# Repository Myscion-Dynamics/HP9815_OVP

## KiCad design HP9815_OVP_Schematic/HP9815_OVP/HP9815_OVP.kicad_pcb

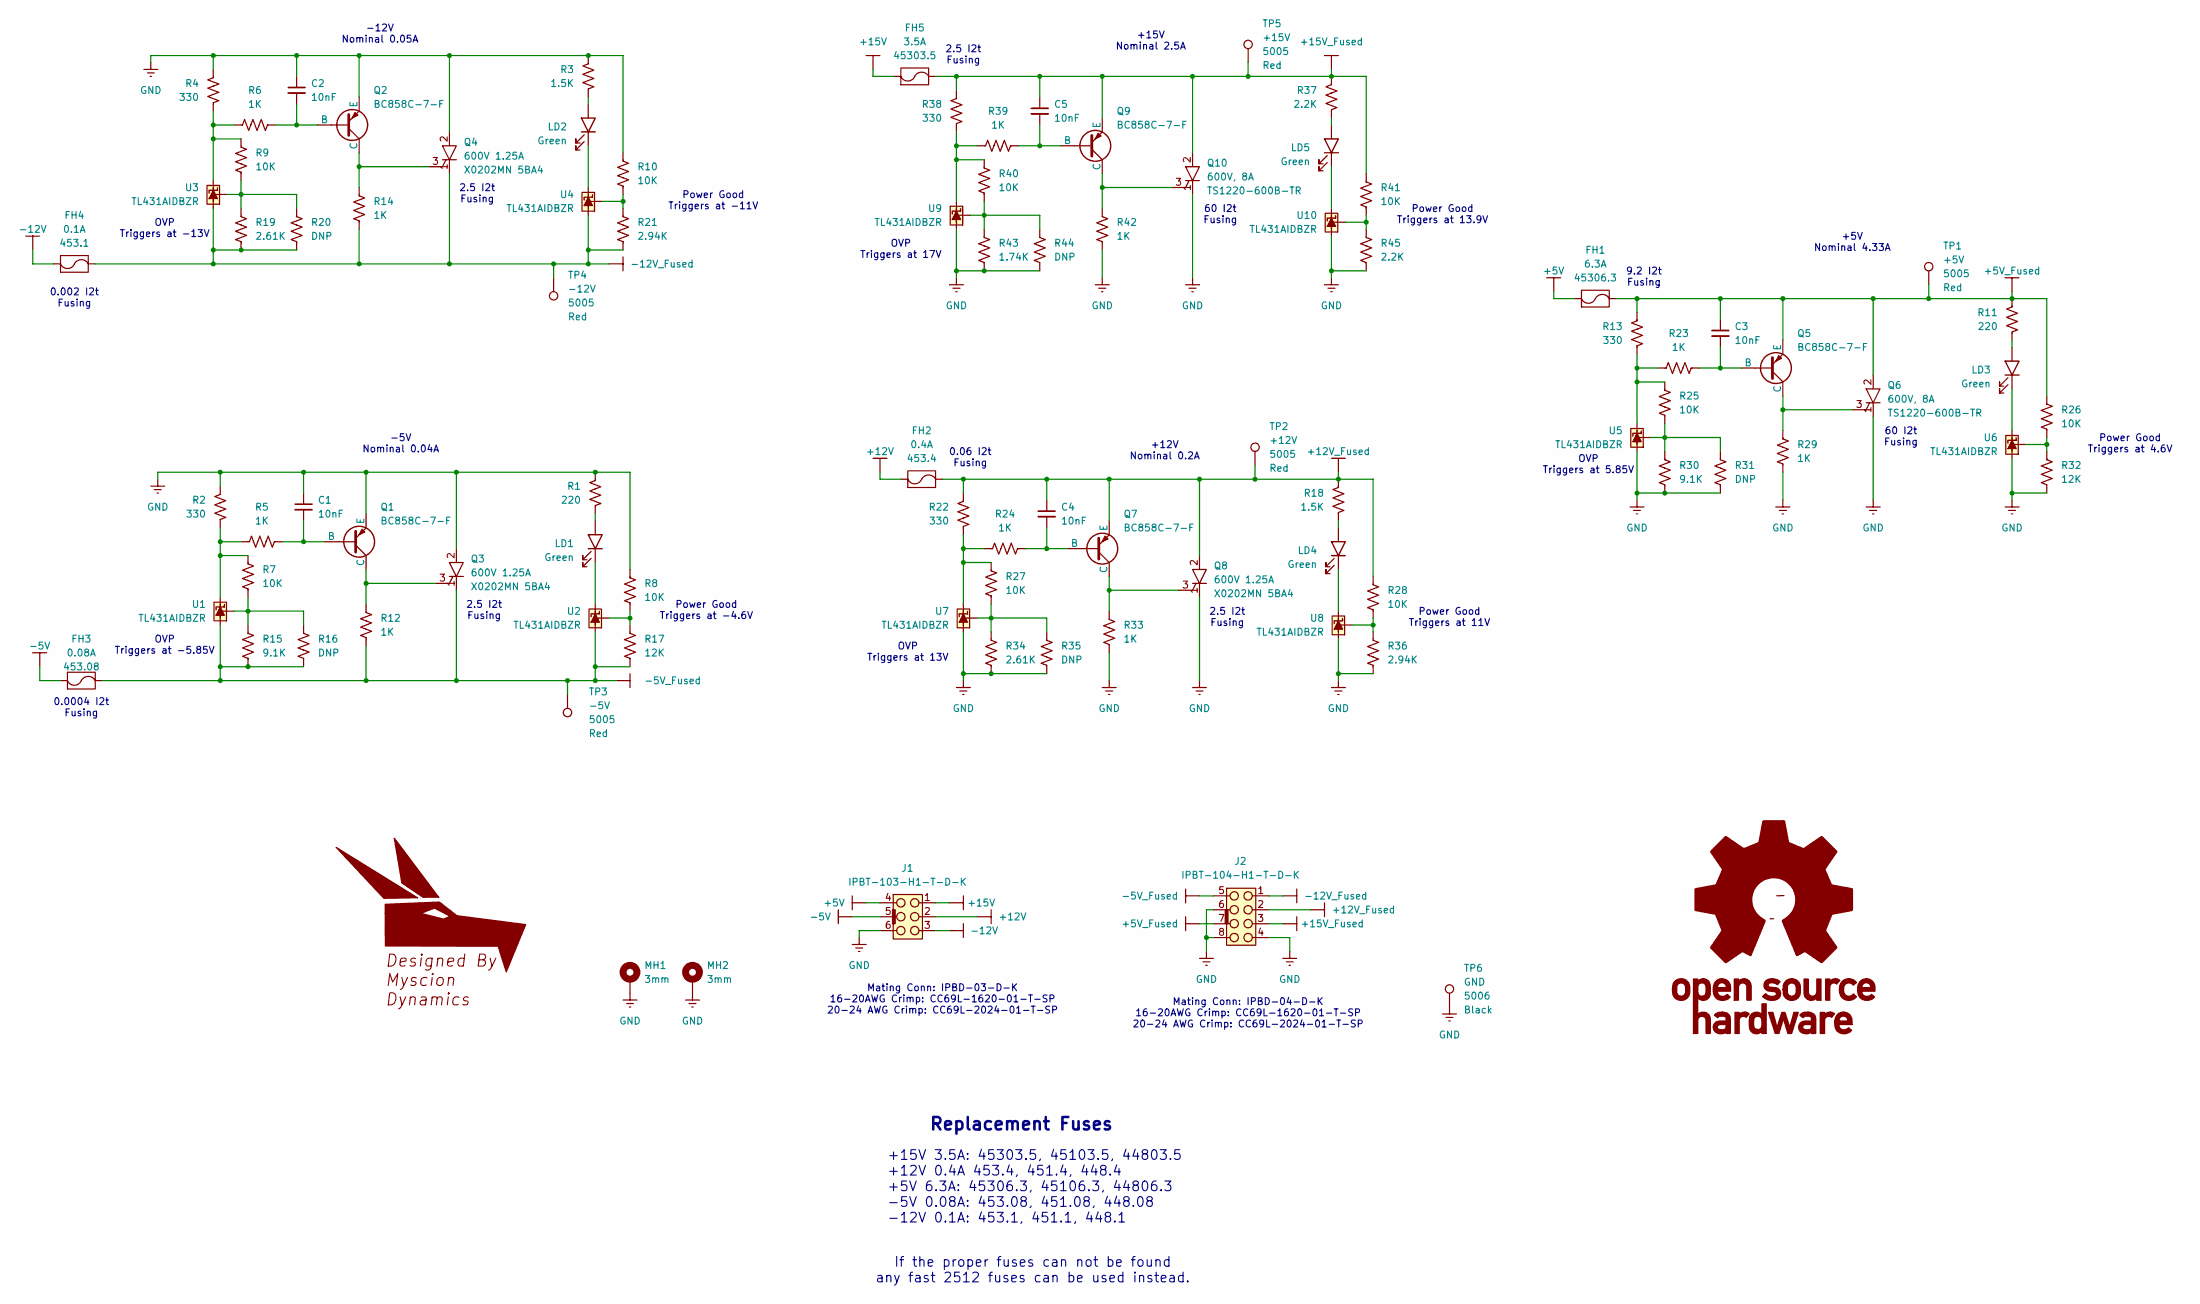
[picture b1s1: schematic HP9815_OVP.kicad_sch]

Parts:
C1, C2, C3, C4, C5: 10nF; C_0603_1608Metric_Pad1.08x0.95mm_HandSolder; Voltage 50V; Tolerance 10%; MPN 311-1085-6-ND
FH1: 6.3A; Fuseholder_Littelfuse_Nano2_154x; Voltage Rating 125V; MPN 15406.3
FH2: 0.4A; Fuseholder_Littelfuse_Nano2_154x; Voltage Rating 125V; MPN 154.4
FH3: 0.08A; Fuseholder_Littelfuse_Nano2_154x; Voltage Rating 125V; MPN 154.08
FH4: 0.1A; Fuseholder_Littelfuse_Nano2_154x; Voltage Rating 125V; MPN 154.1
FH5: 3.5A; Fuseholder_Littelfuse_Nano2_154x; Voltage Rating 125V; MPN 15403.5
GL1: Myscion_Dynamics_Main
GL2: OSHW-Logo_11.4x12mm_SilkScreen
J1: IPBT-103-H1-T-D-K; SAMTEC_IPBT-103-H1-T-D-K; Voltage 400VAC, 565VDC; MPN IPBT-103-H1-T-D-K
J2: IPBT-104-H1-T-D-K; SAMTEC_IPBT-104-H1-T-D-K; Voltage 400VAC, 565VDC; MPN IPBT-104-H1-T-D-K
LD1, LD2, LD3, LD4, LD5: Green; LED_0603_1608Metric_Green_Cath_Dot; MPN HSME-C191
MH1, MH2: 3mm; MountingHole_3.2mm_M3_Pad
Q1, Q2, Q5, Q7, Q9: BC858C-7-F; SOT-23-3_B-E-C; MPN BC858C-7-F
Q3, Q4, Q8: 600V 1.25A; SOT-223-3_TabPin2; MPN X0202MN 5BA4
Q6, Q10: 600V, 8A; TO-252-2; MPN TS1220-600B-TR
R1, R11: 220; R_0603_1608Metric_Pad0.98x0.95mm_HandSolder; MPN RC0603FR-07220RL
R2, R4, R13, R22, R38: 330; R_0603_1608Metric_Pad0.98x0.95mm_HandSolder; MPN RC0603FR-07330RL
R3, R18: 1.5K; R_0603_1608Metric_Pad0.98x0.95mm_HandSolder; MPN RC0603FR-071K5L
R5, R6, R12, R14, R23, R24, R29, R33, R39, R42: 1K; R_0603_1608Metric_Pad0.98x0.95mm_HandSolder; MPN RC0603FR-071KL
R7, R8, R9, R10, R25, R26, R27, R28, R40, R41: 10K; R_0603_1608Metric_Pad0.98x0.95mm_HandSolder; MPN RC0603FR-0710KL
R15, R30: 9.1K; R_0603_1608Metric_Pad0.98x0.95mm_HandSolder; MPN RC0603FR-079K1L
R16, R20, R31, R35, R44: DNP; R_0603_1608Metric_Pad0.98x0.95mm_HandSolder_DNP; MPN NA
R17, R32: 12K; R_0603_1608Metric_Pad0.98x0.95mm_HandSolder; MPN RC0603FR-0712KL
R19, R34: 2.61K; R_0603_1608Metric_Pad0.98x0.95mm_HandSolder; MPN RC0603FR-072K61L
R21, R36: 2.94K; R_0603_1608Metric_Pad0.98x0.95mm_HandSolder; MPN RC0603FR-072K94L
R37, R45: 2.2K; R_0603_1608Metric_Pad0.98x0.95mm_HandSolder; MPN RC0603FR-072K2L
R43: 1.74K; R_0603_1608Metric_Pad0.98x0.95mm_HandSolder; MPN RC0603FR-071K74L
TP1, TP2, TP3, TP4, TP5: TestPoint; TestPoint_Keystone_5005_Compact_Red; MPN 5005
TP6: TestPoint; TestPoint_Keystone_5006_Compact_Black; MPN 5006
U1, U2, U3, U4, U5, U6, U7, U8, U9, U10: TL431DBZ-SOT-23; SOT-23; Tolerance 1%; MPN TL431AIDBZR

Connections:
+5V: FH1.1, J1.4
+5V_Fused: C3.1, FH1.2, J2.7, Q5.E, Q6.2 (A), R11.1, R13.1, R26.1, TP1.1
+12V: FH2.1, J1.2
+12V_Fused: C4.1, FH2.2, J2.2, Q7.E, Q8.2 (A), R18.1, R22.1, R28.1, TP2.1
+15V: FH5.1, J1.1
+15V_Fused: C5.1, FH5.2, J2.3, Q9.E, Q10.2 (A), R37.1, R38.1, R41.1, TP5.1
-5V: FH3.1, J1.5
-5V_Fused: FH3.2, J2.5, Q3.1 (K), R12.1, R15.2, R16.2, R17.2, TP3.1, U1.3 (A), U2.3 (A)
-12V: FH4.1, J1.3
-12V_Fused: FH4.2, J2.1, Q4.1 (K), R14.1, R19.2, R20.2, R21.2, TP4.1, U3.3 (A), U4.3 (A)
GND: C1.1, C2.1, J1.6, J2.4, J2.6, J2.8, MH1.1, MH2.1, Q1.E, Q2.E, Q3.2 (A), Q4.2 (A), Q6.1 (K), Q8.1 (K), Q10.1 (K), R1.1, R2.1, R3.1, R4.1, R8.1, R10.1, R29.1, R30.2, R31.2, R32.2, R33.1, R34.2, R35.2, R36.2, R42.1, R43.2, R44.2, R45.2, TP6.1, U5.3 (A), U6.3 (A), U7.3 (A), U8.3 (A), U9.3 (A), U10.3 (A)
unnamed: C1.2, Q1.B, R5.2
unnamed: C2.2, Q2.B, R6.2
unnamed: C3.2, Q5.B, R23.2
unnamed: C4.2, Q7.B, R24.2
unnamed: C5.2, Q9.B, R39.2
unnamed: LD1.2 (A), R1.2
unnamed: LD1.1 (K), U2.1 (K)
unnamed: LD2.2 (A), R3.2
unnamed: LD2.1 (K), U4.1 (K)
unnamed: LD3.2 (A), R11.2
unnamed: LD3.1 (K), U6.1 (K)
unnamed: LD4.2 (A), R18.2
unnamed: LD4.1 (K), U8.1 (K)
unnamed: LD5.2 (A), R37.2
unnamed: LD5.1 (K), U10.1 (K)
unnamed: Q1.C, Q3.3 (G), R12.2
unnamed: Q2.C, Q4.3 (G), R14.2
unnamed: Q5.C, Q6.3 (G), R29.2
unnamed: Q7.C, Q8.3 (G), R33.2
unnamed: Q9.C, Q10.3 (G), R42.2
unnamed: R2.2, R5.1, R7.1, U1.1 (K)
unnamed: R7.2, R15.1, R16.1, U1.2 (REF)
unnamed: R8.2, R17.1, U2.2 (REF)
unnamed: R4.2, R6.1, R9.1, U3.1 (K)
unnamed: R9.2, R19.1, R20.1, U3.2 (REF)
unnamed: R10.2, R21.1, U4.2 (REF)
unnamed: R13.2, R23.1, R25.1, U5.1 (K)
unnamed: R25.2, R30.1, R31.1, U5.2 (REF)
unnamed: R26.2, R32.1, U6.2 (REF)
unnamed: R22.2, R24.1, R27.1, U7.1 (K)
unnamed: R27.2, R34.1, R35.1, U7.2 (REF)
unnamed: R28.2, R36.1, U8.2 (REF)
unnamed: R38.2, R39.1, R40.1, U9.1 (K)
unnamed: R40.2, R43.1, R44.1, U9.2 (REF)
unnamed: R41.2, R45.1, U10.2 (REF)

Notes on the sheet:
Power Good Triggers at -4.6V
Power Good Triggers at 4.6V
-12V Nominal 0.05A
2.5 I2t Fusing
If the proper fuses can not be found any fast 2512 fuses can be used instead.
OVP Triggers at 13V
Power Good Triggers at 11V
OVP Triggers at -13V
+12V Nominal 0.2A
Replacement Fuses
0.06 I2t Fusing
OVP Triggers at 5.85V
0.002 I2t Fusing
+5V Nominal 4.33A
Power Good Triggers at 13.9V
+15V Nominal 2.5A
Power Good Triggers at -11V
OVP Triggers at 17V
60 I2t Fusing
Mating Conn: IPBD-04-D-K 16-20AWG Crimp: CC69L-1620-01-T-SP 20-24 AWG Crimp: CC69L-2024-01-T-SP
OVP Triggers at -5.85V
-5V Nominal 0.04A
0.0004 I2t Fusing
9.2 I2t Fusing
+15V 3.5A: 45303.5, 45103.5, 44803.5 +12V 0.4A 453.4, 451.4, 448.4 +5V 6.3A: 45306.3, 45106.3, 44806.3 -5V 0.08A: 453.08, 451.08, 448.08 -12V 0.1A: 453.1, 451.1, 448.1
Mating Conn: IPBD-03-D-K 16-20AWG Crimp: CC69L-1620-01-T-SP 20-24 AWG Crimp: CC69L-2024-01-T-SP

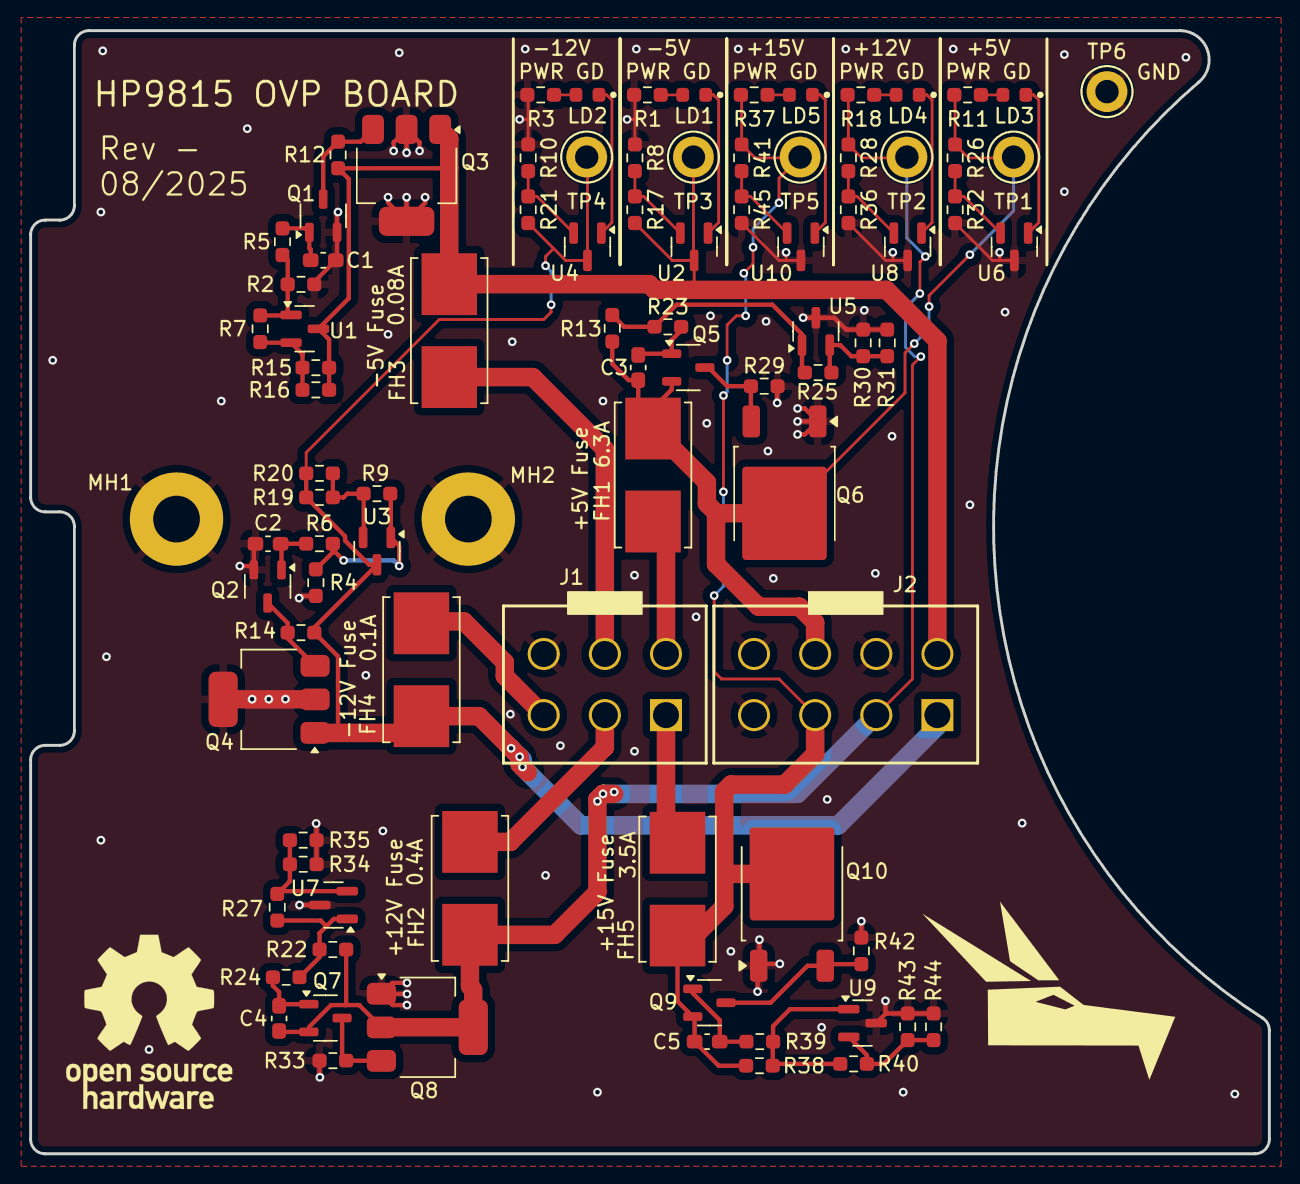
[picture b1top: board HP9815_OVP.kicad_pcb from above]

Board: 2 copper layers, 84.9 x 77.0 mm, 92 parts (0 on the bottom side), 46 nets.

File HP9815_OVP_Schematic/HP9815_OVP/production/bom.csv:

Designator,Footprint,Quantity,Value,LCSC Part #
"C1, C2, C3, C4, C5",0603,5,10nF,311-1085-6-ND
FH1,Fuseholder_Littelfuse_Nano2_154x,1,6.3A,15406.3
FH2,Fuseholder_Littelfuse_Nano2_154x,1,0.4A,154.4
FH3,Fuseholder_Littelfuse_Nano2_154x,1,0.08A,154.08
FH4,Fuseholder_Littelfuse_Nano2_154x,1,0.1A,154.1
FH5,Fuseholder_Littelfuse_Nano2_154x,1,3.5A,15403.5
J1,SAMTEC_IPBT-103-H1-T-D-K,1,IPBT-103-H1-T-D-K,IPBT-103-H1-T-D-K
J2,SAMTEC_IPBT-104-H1-T-D-K,1,IPBT-104-H1-T-D-K,IPBT-104-H1-T-D-K
"LD1, LD2, LD3, LD4, LD5",0603,5,Green,HSME-C191
"MH1, MH2",MountingHole_3.2mm_M3_Pad,2,3mm,
"Q1, Q2, Q5, Q7, Q9",SOT-23-3_B-E-C,5,BC858C-7-F,BC858C-7-F
"Q10, Q6",TO-252-2,2,"600V, 8A",TS1220-600B-TR
"Q3, Q4, Q8",SOT-223-3_TabPin2,3,600V 1.25A,X0202MN 5BA4
"R1, R11",0603,2,220,RC0603FR-07220RL
"R10, R25, R26, R27, R28, R40, R41, R7, R8, R9",0603,10,10K,RC0603FR-0710KL
"R12, R14, R23, R24, R29, R33, R39, R42, R5, R6",0603,10,1K,RC0603FR-071KL
"R13, R2, R22, R38, R4",0603,5,330,RC0603FR-07330RL
"R15, R30",0603,2,9.1K,RC0603FR-079K1L
"R16, R20, R31, R35, R44",0603,5,DNP,NA
"R17, R32",0603,2,12K,RC0603FR-0712KL
"R18, R3",0603,2,1.5K,RC0603FR-071K5L
"R19, R34",0603,2,2.61K,RC0603FR-072K61L
"R21, R36",0603,2,2.94K,RC0603FR-072K94L
"R37, R45",0603,2,2.2K,RC0603FR-072K2L
R43,0603,1,1.74K,RC0603FR-071K74L
"TP1, TP2, TP3, TP4, TP5",TestPoint_Keystone_5005_Compact_Red,5,TestPoint,5005
TP6,TestPoint_Keystone_5006_Compact_Black,1,TestPoint,5006
"U1, U10, U2, U3, U4, U5, U6, U7, U8, U9",SOT-23,10,TL431DBZ-SOT-23,TL431AIDBZR

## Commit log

2025-08-22 Added PCB tracing file
2025-08-22 Identifed -12 and -5V taps
2025-08-24 Simulated started and outline done
2025-08-25 simulation proof of concept working
2025-08-29 Commit before relinking ref des
2025-08-30 First draft of layout
2025-08-31 Ready to send to production
2025-09-01 Sent PCB out to fab
2025-09-08 added drawing for wiring harness
2025-09-12 Added IBOM
